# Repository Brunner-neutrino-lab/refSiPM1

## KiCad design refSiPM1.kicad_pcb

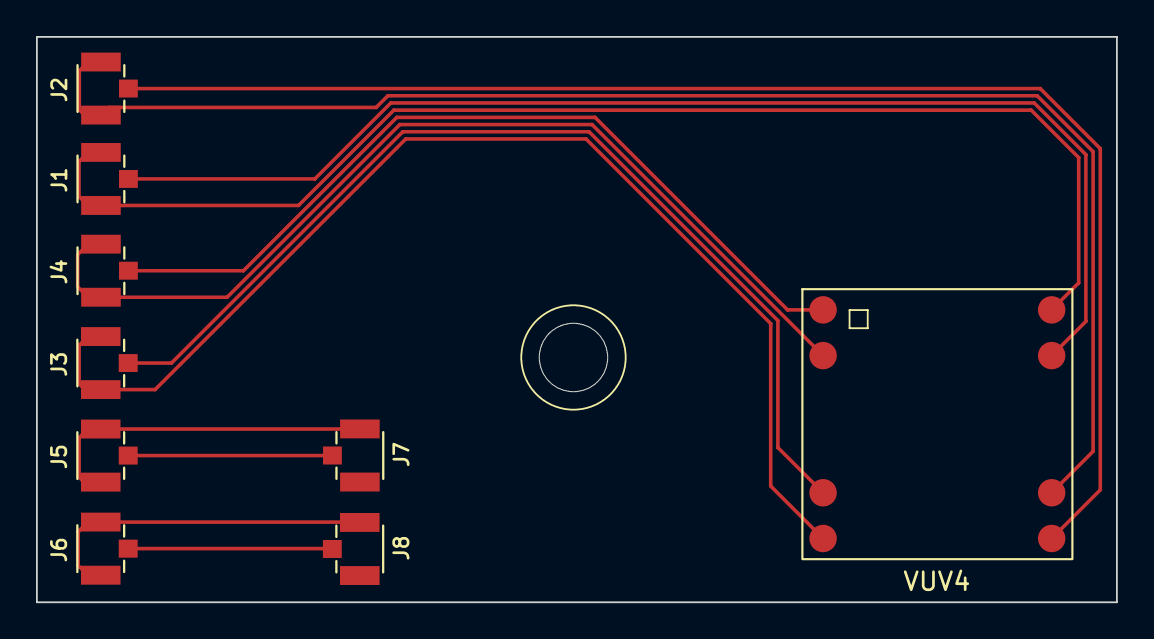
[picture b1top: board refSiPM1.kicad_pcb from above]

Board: 2 copper layers, 60.0 x 31.4 mm, 9 parts (0 on the bottom side), 12 nets.

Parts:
J1, J2, J3, J4, J5, J6, J7, J8: U.FL-R-SMT-1_10_; HRS_U.FL-R-SMT-1_10_
VUV4: VUV4-50q

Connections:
unnamed: J1.1, J1.3, VUV4.1 (A)
unnamed: J1.2, VUV4.5
unnamed: J2.1, J2.3, VUV4.2 (A)
unnamed: J2.2, VUV4.6
unnamed: J4.1, J4.3, VUV4.4 (A)
unnamed: J4.2, VUV4.8
unnamed: J3.1, J3.3, VUV4.3 (A)
unnamed: J3.2, VUV4.7
unnamed: J5.1, J5.3, J7.1, J7.3
unnamed: J5.2, J7.2
unnamed: J6.1, J6.3, J8.1, J8.3
unnamed: J6.2, J8.2

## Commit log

2024-10-14 Initial upload with PCB files
2024-10-15 adjusted traces and added silkscreen
